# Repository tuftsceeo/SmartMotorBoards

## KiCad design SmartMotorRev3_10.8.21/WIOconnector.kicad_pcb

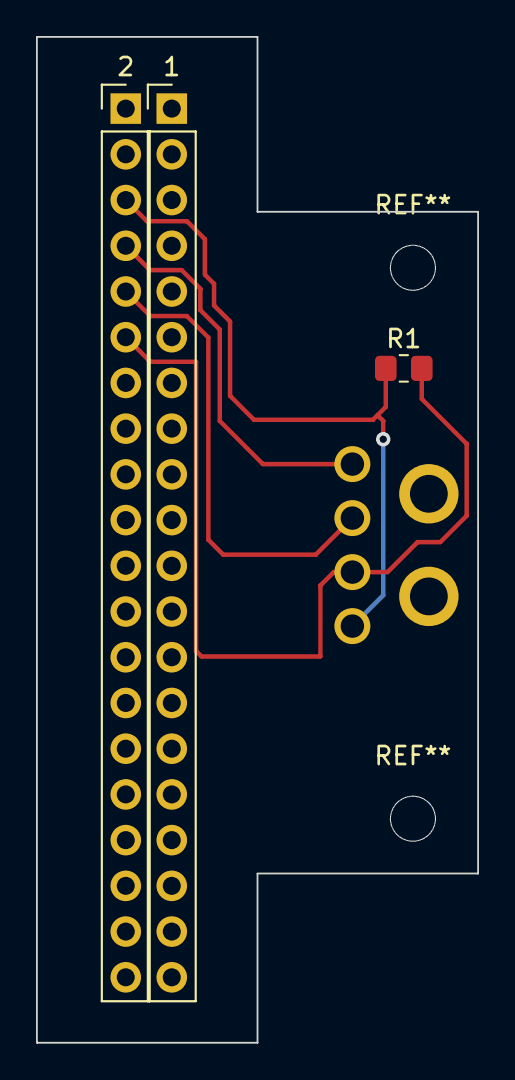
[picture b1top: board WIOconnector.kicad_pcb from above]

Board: 2 copper layers, 24.5 x 55.9 mm, 4 parts (1 on the bottom side), 4 nets.

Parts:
1, 2: Conn_01x20_Male; PinHeader_1x20_P2.54mm_Vertical
Motor Connection: Conn_01x04_Male; TE_Connectivity_AMP_Connectors
R1: R; R_0805_2012Metric_Pad1.20x1.40mm_HandSolder

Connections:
unnamed: 2.3, Motor Connection.4, R1.1
unnamed: 2.4, Motor Connection.1
unnamed: 2.5, Motor Connection.2
unnamed: 2.6, Motor Connection.3, R1.2

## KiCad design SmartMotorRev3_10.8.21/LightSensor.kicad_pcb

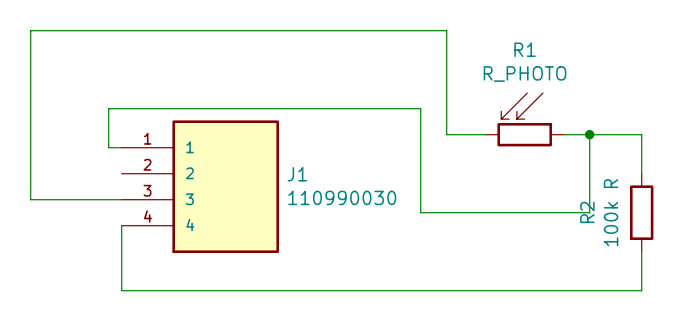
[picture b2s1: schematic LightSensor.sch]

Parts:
J1: 110990030; SEEED_110990030; PARTREV A
R1: R_PHOTO; R_Axial_DIN0309_L9.0mm_D3.2mm_P2.54mm_Vertical
R2: 100k R; R_0805_2012Metric_Pad1.20x1.40mm_HandSolder

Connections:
unnamed: J1.1, R1.1, R2.1
unnamed: J1.3, R1.2
unnamed: J1.4, R2.2

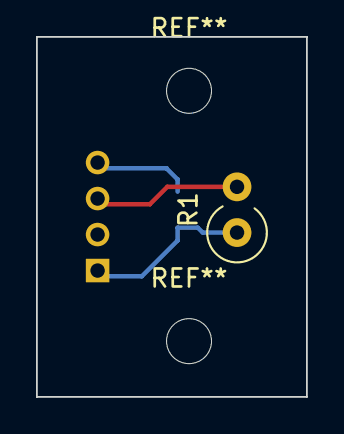
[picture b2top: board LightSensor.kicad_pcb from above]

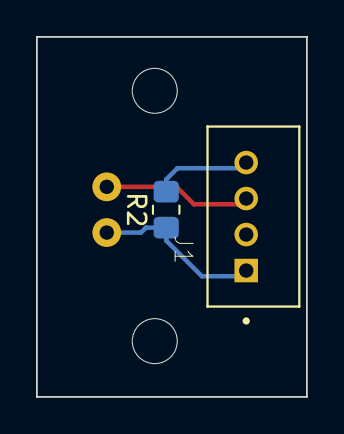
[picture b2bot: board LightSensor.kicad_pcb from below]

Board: 2 copper layers, 15.0 x 20.0 mm, 3 parts (2 on the bottom side), 3 nets.

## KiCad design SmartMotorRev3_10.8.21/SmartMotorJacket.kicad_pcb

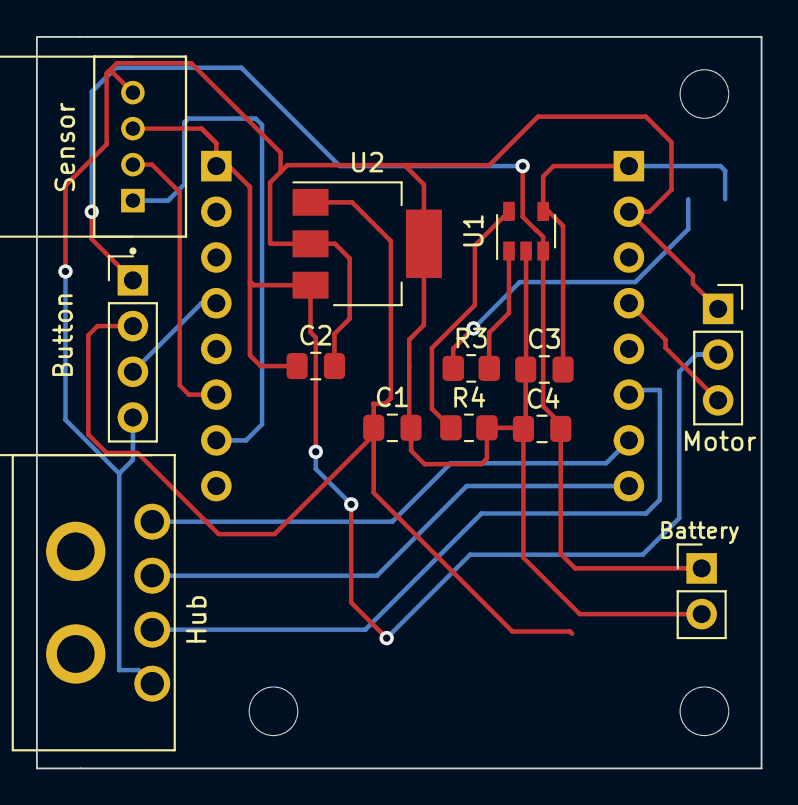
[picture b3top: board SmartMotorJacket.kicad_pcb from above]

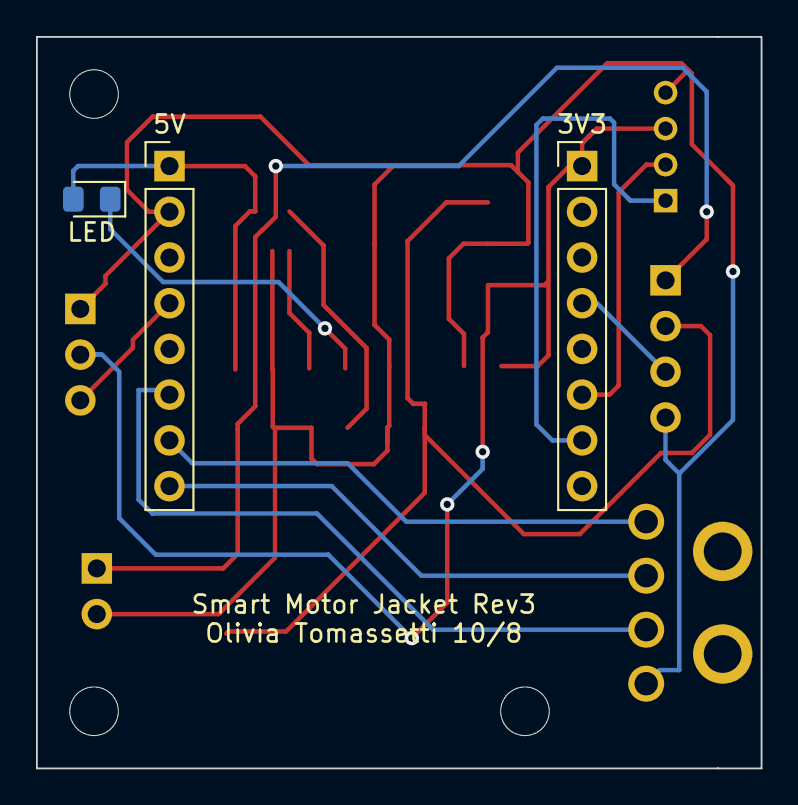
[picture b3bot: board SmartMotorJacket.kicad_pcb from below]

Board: 2 copper layers, 40.3 x 40.6 mm, 16 parts (3 on the bottom side), 15 nets.

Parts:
3V3: Right Pinout; PinHeader_1x08_P2.54mm_Vertical
5V: Left Pinout; PinHeader_1x08_P2.54mm_Vertical
Battery: Battery Port; PinHeader_1x02_P2.54mm_Vertical
Button: Conn_01x04_Male; PinHeader_1x04_P2.54mm_Vertical
C1, C2, C3, C4: 4.7 uF C; C_0805_2012Metric_Pad1.18x1.45mm_HandSolder
Hub: Hub Port; TE_Connectivity_AMP_Connectors
LED: LED; LED_0805_2012Metric_Pad1.15x1.40mm_HandSolder
Motor: Motor Connector; PinSocket_1x03_P2.54mm_Vertical
R3: 470 R; R_0805_2012Metric_Pad1.20x1.40mm_HandSolder
R4: 2k R; R_0805_2012Metric_Pad1.20x1.40mm_HandSolder
Sensor: Sensor Port; SEEED_110990030
U1: MCP73831-2-OT; SOT-23-5
U2: AP7361C-33E; SOT-223-3_TabPin2

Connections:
+BATT: Battery.1, Button.1, C4.1, U1.3
/ADC0: 3V3.7, Sensor.1
/GPIO2-LED: 5V.4, Motor.3
/GPIO3: 5V.7, Hub.1
/GPIO5: 5V.6, Hub.3
/GPIO13: 3V3.4, Button.3
/GPIO14: 3V3.6, Sensor.2
GND: 5V.2, Battery.2, Button.4, C1.2, C2.2, C3.1, C4.2, Hub.4, Motor.1, R4.2, Sensor.4, U1.2, U2.2
unnamed: Button.2, C1.1, U2.1
unnamed: 3V3.1, C2.1, Motor.2, Sensor.3, U2.3
unnamed: 5V.1, C3.2, LED.2, U1.4
unnamed: LED.1, R3.1
unnamed: 5V.8, Hub.2
unnamed: R3.2, U1.1
unnamed: R4.1, U1.5

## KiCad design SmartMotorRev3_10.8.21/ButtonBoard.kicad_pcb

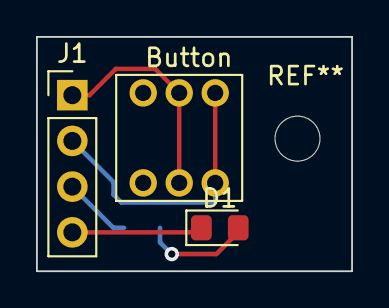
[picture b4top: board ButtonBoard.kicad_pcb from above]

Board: 2 copper layers, 17.5 x 13.0 mm, 4 parts (1 on the bottom side), 5 nets.

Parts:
Button: SW_Push_DPDT; DPDT Latching Push Button
D1: LED; LED_0805_2012Metric_Pad1.15x1.40mm_HandSolder
J1: Conn_01x04_Male; PinHeader_1x04_P2.54mm_Vertical
R1: R; R_0805_2012Metric_Pad1.20x1.40mm_HandSolder

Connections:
GND: D1.1, J1.4
unnamed: D1.2, R1.2
unnamed: Button.2, Button.5, J1.1
unnamed: Button.3, Button.6, J1.2
unnamed: J1.3, R1.1

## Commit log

2022-05-25 board
